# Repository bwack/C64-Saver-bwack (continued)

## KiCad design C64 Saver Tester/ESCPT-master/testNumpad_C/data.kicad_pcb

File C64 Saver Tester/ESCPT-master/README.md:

Tool to Draw Electrostatic Capacitive Pad on KiCAD
====
This tool helps you to make pads for mutual capacitance method on Pcbnew 
application. If you use bitmap to component converter to make pads, 
you can not use DRC well. But this macro draws pads as zone, so you can use 
DRC to check design rules on your PCB.

This is just a tool to provide the easy way to make pad on PCB. 
No case, no additional hardware and no firmware are provided.

Decide parameters for pads yourself. Default parameters might be useless.

There are some restrictions: 
* Only a type pad can be used on a single PCB design.
* Remove all elements before you change pad type.
* There are some test KiCAD project in this repository but do not try to reuse their design. They have never tested.

## Usage

1. Copy ESC_Pads.lib on your workspace and specify it to be used by the Eeschema.
2. Copy ESC_Pads.pretty directory with its contents and specify they can be found by the Pcbnew.
3. Draw circuit on Eeschema using symbols from ESC_Pads.lib.
4. Bind between symbols and modules.
5. Load nets into the Pcbnew.
6. Layout modules on your own.
7. Execute macro contained in the ESCP_Tool.py file.
8. Add zone GND on your PCB.
9. Execute DRC to make your PCB clean.
10. Route between pads and between pads and components.
11. Fill copper again or execute DRC if you required.

* Remove all elements add again if you move or rotate pad module.

See the following sections for more detail.

## Macro
You can execute the macro through Pcbnew - Tools - Scripting Console. 
Execute clipboard content through context menu on the console if you use KiCAD 4.0.

If you use development version of KiCAD, helper tool: 
https://gist.github.com/hanya/08591a20a6c76bf9215f8175bd46681b

* Settings: you can load and store your parameter settings.
* Pad type: type of pad, choose this type to match with modules you have choosen.
* Reference pattern: regular expression pattern to be matched with your modules.
* Outer radius: radius of your pad.
* Pad radius: radius of inner pads.
* Gap width: width of separation between inner pads, this does not contain zone clearance.
* Gap center width: thinner separation between through holes, this parameter is used only for type A.
* Gap center radius: radius of inner arc for inner pads.
* Corners: number of corners for arc or circular zones, 64 is enough in general.
* Zone Clearance: clearance setting of zone pads.
* Zone minimum width: minimum width setting of zone pads.
* GND tracks: add or remove separation GND between inner pads.
* Zone pads: add or remove inner pads as zones.
* Front keepout: add or remove outer keepout zone.
* Back keepout: add or remove keepout zone to avoid copper pour.
* All: Add or remove all above four elements.

Please keep in mind that zone clearance is added around zones added by the macro. 
If gap between pads or zones is thinner than zone minimum width, no copper is poured.

## Type A
This type of pad contains set of pads with through hole and separated by the middle line of GND.

## Type B
No through hole on pads.

* Gap center width parameter is not used on this pad.

## Type C
Just like type B but with the middle separator on the back side. 
Meaning of all parameters are the same with the type B.

## How to make own pad module

* For type A, place SMD pads near each through hole pads. They helps to connect between through hole pad and zone.
* Width of pad 0 used for GND should be thinner than gap width.
* Place GND SMD pads to indicate start and end of gap on both side for type A and C.
* Set pad connection type to solid which is embedded in zones.

## License
Macros are licensed under GPLv3.

Symbols for the Eeschema and modules for the Pcbnew are placed under Public Domain.

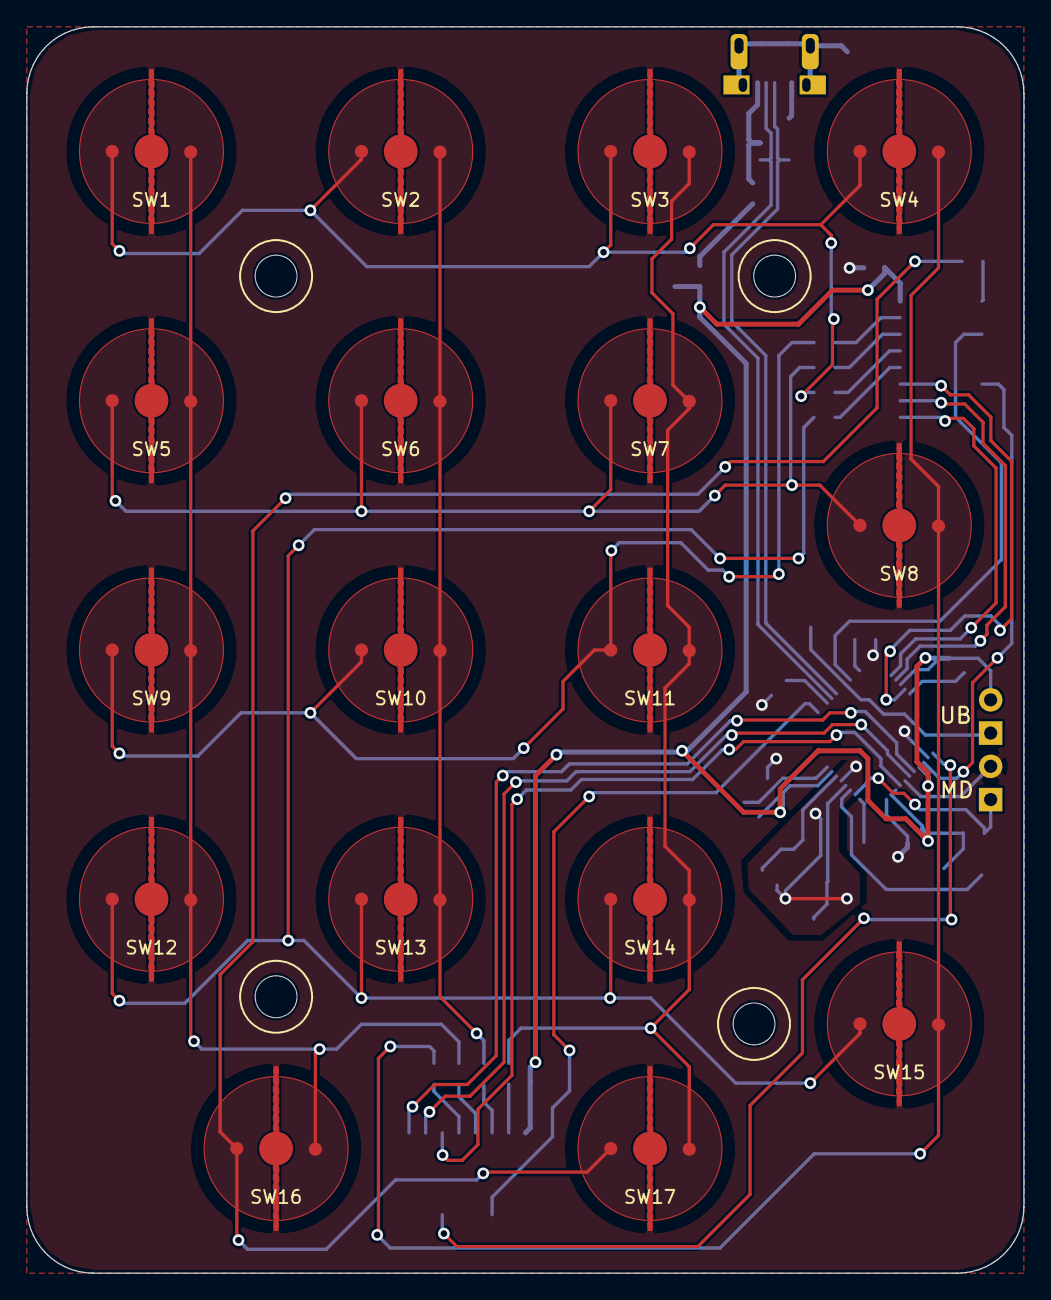
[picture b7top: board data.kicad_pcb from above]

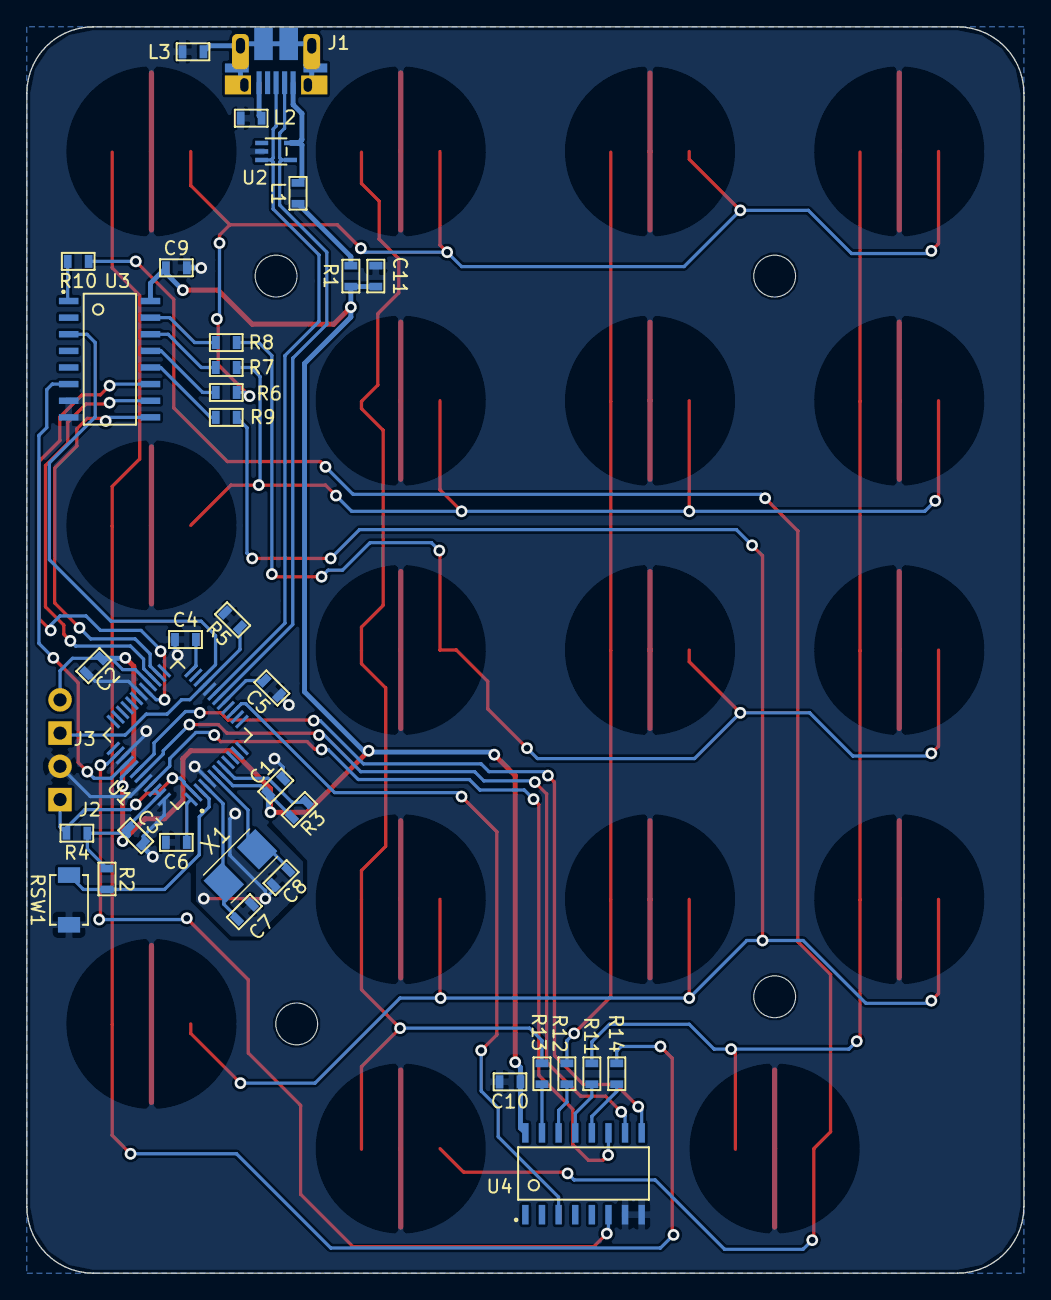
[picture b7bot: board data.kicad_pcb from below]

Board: 2 copper layers, 76.2 x 95.2 mm, 58 parts (37 on the bottom side), 45 nets.

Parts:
C1, C2, C3, C9, C10: 100n; 0603_1608
C4: 10n; 0603_1608
C5: 330n; 0603_1608
C6, C11: 4u7; 0603_1608
C7, C8: 4p; 0603_1608
J1: MicroB; 10103594
J2, J3: CON2; J2
L1, L2, L3: INDUCTOR2; 0603_1608
R1: Polyswitch; 0603_1608
R2, R4: 4K7; 0603_1608_R
R3, R5: 10K; 0603_1608_R
R6, R7, R8, R9, R10, R11, R12, R13, R14: 470; 0603_1608_R
RSW1: SWITCH; TD_85XU
SR1, SR2, SR3, SR4: M3; M3NP
SW1, SW2, SW3, SW4, SW5, SW6, SW7, SW8, SW9, SW10, SW11, SW12, SW13, SW14, SW15, SW16, SW17: ESC_Pad_B; ECS_Pad_B
U1: R5F5231XAXFL; LQFP48-0.5
U2: DF5A6.8; SOT353
U3, U4: 74HC4051; SOIC16
X1: 12MHz; Crystal_5032

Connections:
/COL: U1.15, U4.3
/COL0: R11.1, SW1.2, SW5.2, SW9.2, SW12.2, SW16.2
/COL1: R12.1, SW2.2, SW6.2, SW10.2, SW13.2
/COL2: R13.1, SW3.2, SW7.2, SW11.2, SW14.2, SW17.2
/COL3: R14.1, SW4.2, SW8.2, SW15.2
/COL_A: U1.45, U4.11
/COL_B: U1.43, U4.10
/COL_C: U1.42, U4.9
/COL_INH: U1.38, U4.6
/MD: J2.1, R4.2, U1.2
/RESET: R2.2, RSW1.1, U1.3
/ROW: U1.22, U3.3
/ROW1: R6.1, SW1.1, SW2.1, SW3.1, SW4.1
/ROW2: R7.1, SW5.1, SW6.1, SW7.1, SW8.1
/ROW3: R8.1, SW9.1, SW10.1, SW11.1
/ROW4: R9.1, SW12.1, SW13.1, SW14.1, SW15.1
/ROW5: R10.1, SW16.1, SW17.1
/ROW_A: U1.29, U3.11
/ROW_B: U1.27, U3.10
/ROW_C: U1.26, U3.9
/ROW_INH: U1.40, U3.6
/TSCAP: C4.2, U1.24
/UB: J3.1, R5.1, U1.21
/USB_DM: J1.2, U1.18, U2.4
/USB_DP: J1.3, U1.19, U2.3
/VBUS: J1.1, L1.2, U2.5
GND: C1.2, C2.2, C3.2, C4.1, C5.1, C6.2, C7.2, C8.2, C9.2, C10.2, C11.2, J2.2, L2.1, L3.1, R5.2, RSW1.2, SW1.0, SW2.0, SW3.0, SW4.0, SW5.0, SW6.0, SW7.0, SW8.0, SW9.0, SW10.0, SW11.0, SW12.0, SW13.0, SW14.0, SW15.0, SW16.0, SW17.0, U1.5, U1.20, U1.30, U1.39, U1.44, U1.48, U2.2, U3.7, U3.8, U4.7, U4.8
unnamed: C5.2, U1.17
unnamed: C6.1, U1.1
unnamed: C7.1, U1.4, X1.2
unnamed: C8.1, U1.6, X1.1
unnamed: J1.5, L2.2
unnamed: J1.6, L3.2
unnamed: L1.1, R1.1
unnamed: R3.1, U1.8
unnamed: R6.2, U3.13
unnamed: R7.2, U3.14
unnamed: R8.2, U3.15
unnamed: R9.2, U3.12
unnamed: R10.2, U3.1
unnamed: R11.2, U4.13
unnamed: R12.2, U4.14
unnamed: R13.2, U4.15
unnamed: R14.2, U4.12
VCC: C1.1, C2.1, C3.1, C9.1, C10.1, C11.1, J3.2, R1.2, R2.1, R3.2, R4.1, U1.7, U1.28, U1.41, U1.46, U1.47, U3.16, U4.16

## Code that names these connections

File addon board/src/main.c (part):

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//#include "tinyavrlib/cpufreq.h"
//#define F_CPU 8000000UL    // 8 MHz

#define SSD1306_SCL   PB2
#define SSD1306_SDA   PB0
#define HOLD_N        PB1
#define HOLD_ON       PORTB |= (1 << HOLD_N)
#define HOLD_OFF      PORTB &= ~(1 << HOLD_N)
#define SSD1306_SA    0x78  // Slave address
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
void init(void) {
  conf.oc=12; // 1.2A
  conf.hold=1; // 1=hold, 0=autorecover
  conf.vtrip=55; // 5.5V

  uint8_t ee_oc=255, ee_hold=255, ee_vtrip=255;
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  MCUCR &= ~(1 << PUD);

  // set SDA and SCL to tri-state
  DDRB &= ~((1 << PB0) | (1 << PB2));
  PORTB &= ~((1 << PB0) | (1 << PB2));

  // wait a bit until everything stabilises
  _delay_ms(40);
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
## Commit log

2018-06-13 inital commit 1.0 saver
2018-06-13 1.1 to 1.3
2018-06-17 C64 Saver 2 first commit
2018-06-17 Tidy up project libraries. Relative paths
2018-06-22 layed out and routed
2018-06-22 schematic pdf and image of pcb
2018-06-24 readme
2018-06-25 LICENSE, Changelog
2018-06-25 Name, revision, author on silk.s
2018-06-25 revision on addon board
2018-06-25 deleted backup file
2018-06-25 deleted .bak file
2018-07-02 dimensions
2018-07-02 saver 2.0beta - addon 1.0beta
2018-07-02 added gnd, 5x 9vac pins, moved c1 closer to input circuit
2018-07-03 eddited schematic of addon board
2018-07-04 SOP4 model
2018-07-05 ssop. 0603 capacitors
2018-07-05 another regulator on 5v to protect the ina219 and iso1541
2018-07-08 fit to hammond1591, larger board.
2018-07-08 hammond1551G. It will be a tight fit !
2018-07-10 addon board component placement done. layout begun.
2018-07-11 more routing. mostly power nets remaining
2018-07-12 routing completed
2018-07-12 included 2.0beta (throughhole) and 2.1 smd is the upcomming version
2018-07-22 Release 2.1 and addon 1.0
2018-08-08 Editting V2.2. R1 was rotated. why.
2018-08-08 Remove gerbers from sources. See Releases for gerbers.
2018-08-08 Ignore gerber
2018-08-09 resistor values
2018-08-09 date and version
2018-08-16 release saver v2.2
    got fix for rotated resistor
2018-08-16 merge
2018-08-18 v2.3
2018-09-02 working makefile and helloworld example
2018-09-08 Change: ATtiny footprint, ADC used with reset input
2018-09-08 Added Adam Honse's USI I2C Slave Master library for ATTiny
2018-09-09 Board rerouted
2018-09-09 modified usi_i2c_master to support attiny85
2018-09-16 The i2c in i2c_master and sd1306 source code does not go well together
    might want to rewrite the code for the sd1306 and use the usi_i2c_master library. Might be slower though.
2018-09-16 c64 saver 2 bom with elfa order numbers
2018-09-16 BOM for the addon board
2018-09-16 bom addon board
2018-09-16 female male
2018-09-23 New layout new routing. Resistor divider to support low Vth. #13
2018-09-23 I suppose saving the design helps #13
2018-09-23 Addon board ready for new release #9
2018-09-23 type
2018-09-24 WTF, text on titleblock on copper layer???
2018-10-02 testing the 8x16 font and num2str.c
2018-10-09 Rotated 3D drawing of D1 on addon board
    Rotated only the 3D drawing of D1. The layout is the same.
2018-10-19 troubleshooting INA I2C
2018-10-19 cleanup
2018-10-20 removed usi_i2c_master added INA I2C INA I2C works now but MCU still hangs if OLED I2C is used too
2018-10-20 removed usi_i2c_master
2018-10-20 INA I2C works as standalone but MCU freezes when INA I2C is used with ssd1306 I2C
2018-10-21 actually, INA219 is not responding on any port
2018-10-21 fixed CPU clock improved I2C timings
2018-10-21 improved ACK/NAK timing
2018-10-21 further I2C timing improvements
2018-10-22 repeatedly detecting INA219 in infinite loop
2018-10-23 more i2c timing improvements
2018-11-01 still troubleshooting INA I2C
2018-11-01 added stop condition on startup to prevent i2c garbage interference
2018-11-03 still troubleshooting and still no life signs from INA
2018-11-04 addonboard: 5V moved to VIN+, and fixed SDA2 and SCL2. #16 #17
2018-11-04 work in progress
2018-11-04 troubleshooting SDA always high bug
2018-11-08 4k7 pullups + readme
2018-11-08 old code
2018-11-11 Swapped HOLD_ with SENSE_VAC #18
2018-11-30 main loop timing, button logic, AC adc. Worked out warnings (-Werror).
2018-12-02 Firmware: New features
2018-12-02 Firmware: Settings on EEPROM.
2019-01-05 release firmware 1.0
2019-05-19 bom update
2019-05-20 MLCC 1210 cap and optoisolators changed to Package_SO:SOIC-4_4.55x2.6mm_P1.27mm
    Not finished routing. Needs more of the 1210 caps.
2019-05-23 Addon Board 1.3 (2019-05-24)
    - Changed optocoupler footprint to more common SOIC-4_4.55x2.6mm_P1.27mm
    - Larger 5V regulator on 9vac side for less heat
    - replaced 100uF tantalum with 3x 47uF 1206 MLCC
    - kicad 5.1.0 project
2019-05-23 screenshot of the board
2019-05-24 year and version on silkscreen
    switched to kicad 5.1.0 -> 5.1.2
2019-06-23 kicad 5.1.0 -> 5.1.2
2019-07-16 Delete C64Saver2-addon-BOM.txt
    Double documentation !
2019-07-16 Revert "Delete C64Saver2-addon-BOM.txt"
    This reverts commit ba7545e9be7d77e44fc48137fce718ff76d0ae6d.
2019-08-25 Relay Hold Addon Board 0.2
2020-02-13 Updated readme with BOM
2020-08-29 Updated bom is in the readme. This bom file was outdated. Deleteing it.
2020-08-29 Added IN/OUT to bottom silkscreen. upped project to Kicad 5.1.2
2020-09-12 C64 Saver 2.5 ready for prototype
2020-09-12 the drill file
2020-09-13 Added old v2.4 files in C64 Saver 2.4 folder
2020-09-27 pdf update
2020-09-27 test
2020-09-27 sometest
2022-02-08 added 3D images and fixed readme #27
2023-03-20 THT 2.6 update. renamed some folders to separate SMD and THT versions.
2023-03-20 some deleted folders
2023-03-20 removed the c64 saver tester project.
2023-03-21 SMD version 2.6 layout and schematics. Both THT and SMD are now on same version. should have same references.
2023-03-22 layout for tht 2.6. added connector for leds as alternative to smd leds
2023-03-25 Updated Throughole version (2.6). Gerbers, BOM, PDF etc. Moved old versions to folders. Might remove later
2023-04-01 Preparing for Saver 2.6, moving 2.5 and 2.4 to oldfiles folder
2023-04-02 finished OCP version ready for testing
2023-04-02 added digi-key order numbers to ibom
2023-04-02 Added ibom for addon board, and put the elfa+RS components into the parts/ibom
2023-04-02 updated schematics pdfs
2023-10-18 Redesign with improvements: - LED2 pulling from 5V_SAFE to avoid higher V on pin1 of Q1. This had an effect of reduce the on saturation of Q2 and limiting overall current slightly. Also this allows a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
2023-10-20 Renamed folder to remove version number and moved easyeda to own folder in prep for kicad version. No code changes.
2023-10-20 Adding 2.6 to folder (so the difference is visible in a PR)
2023-10-20 2.7 with iBom and gerbers
2023-11-19 Updates to both kicad and easyeda versions. I found a missing connection in the earlier untested Kicad version. :(
2023-11-19 Missed the easyeda main files.
2023-11-19 Strictly moved folders, no changes to files, to better mirror Bwack's original format of folders.
2023-11-19 Version 2.7 of the through hole version, squashed merge for cleanliness.
